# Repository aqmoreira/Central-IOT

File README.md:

# Central-IOT
Central Semafórica IOT - Projeto Hardware e Software UNIVESP

Projeto focado em explorar e praticar conceitos desenvolvidos no curso de Engenharia da Computação da UNIVESP, apresentado como projeto de TCC em Grupo.
<br>

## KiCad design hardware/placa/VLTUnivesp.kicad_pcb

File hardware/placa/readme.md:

A placa foi desenvolvida com Kicad 5.1.6

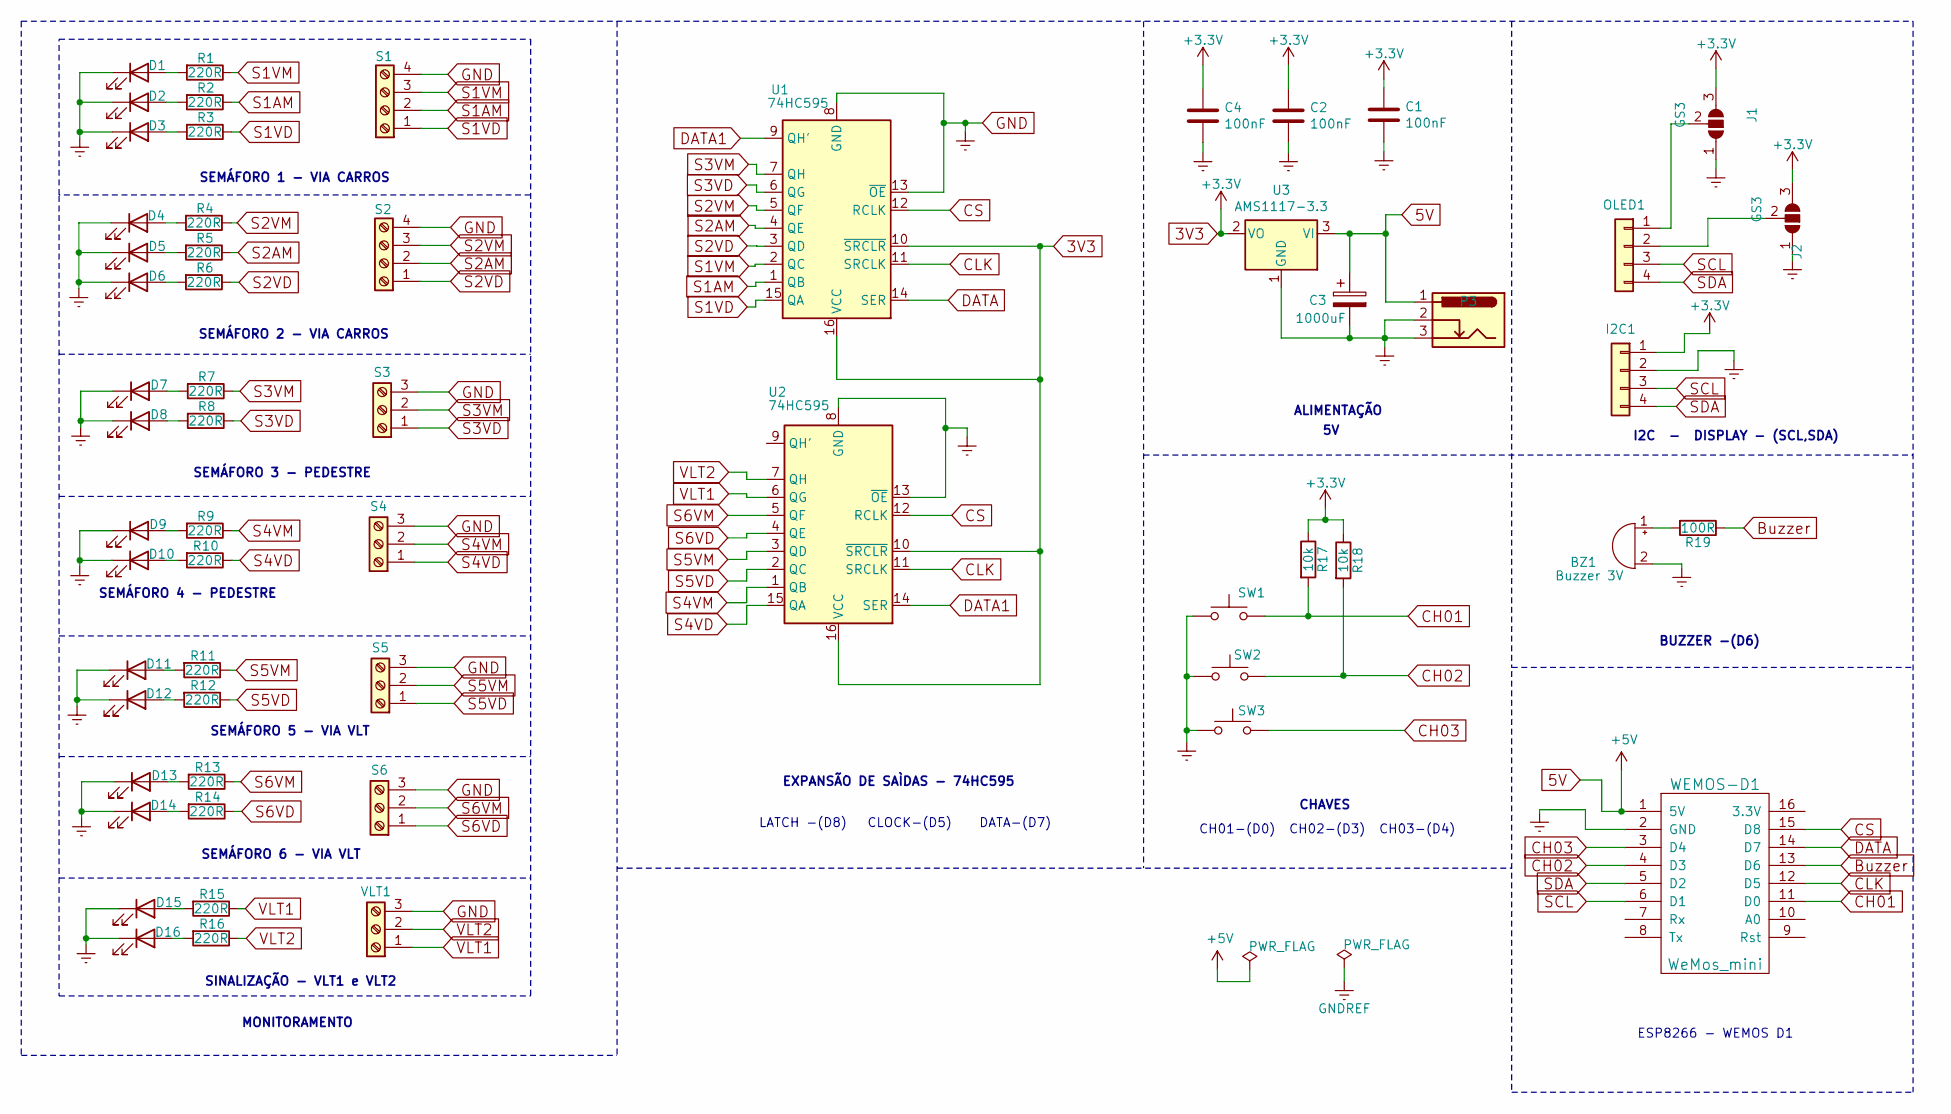
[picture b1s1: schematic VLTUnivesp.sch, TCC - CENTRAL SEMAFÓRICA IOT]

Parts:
BZ1: Buzzer 3V; Buzzer_12x9.5RM7.6
C1, C2, C4: 100nF; C_Disc_D5.0mm_W2.5mm_P5.00mm
C3: 1000uF; CP_Radial_D10.0mm_P7.50mm
D1, D4, D7, D9, D11, D13: LED; LED_D5.0mm_VM
D2, D5: LED; LED_D5.0mm_AM
D3, D6, D8, D10, D12, D14: LED; LED_D5.0mm_VD
D15: LED; LED_D5.0mm_AZ
D16: LED; LED_D5.0mm_LA
I2C1: CONN_01X04; PinSocket_1x04_P2.54mm_Vertical
J1, J2: GS3; SolderJumper-3_P1.3mm_Open_RoundedPad1.0x1.5mm_NumberLabels
OLED1: CONN_01X04; PinSocket_1x04_P2.54mm_Vertical
P3: CONN_01X03; BarrelJack_Horizontal
R1, R2, R3, R4, R5, R6, R7, R8, R9, R10, R11, R12, R13, R14, R15, R16: 220R; R_Axial_DIN0204_L3.6mm_D1.6mm_P7.62mm_Horizontal
R17, R18: 10k; R_Axial_DIN0204_L3.6mm_D1.6mm_P7.62mm_Horizontal
R19: 100R; R_Axial_DIN0204_L3.6mm_D1.6mm_P7.62mm_Horizontal
S1, S2: Screw_Terminal_01x04; KRE-1x04_P5.00mm_Horizontal
S3, S4, S5, S6: Screw_Terminal_01x03; KRE-1x03_P5.00mm_Horizontal
SW1, SW2, SW3: SW_PUSH; SW_PUSH_6mm
U1, U2: 74HC595; DIP-16_W7.62mm
U3: AMS1117-3.3; SOT-223-3_TabPin2
VLT1: Screw_Terminal_01x03; KRE-1x03_P5.00mm_Horizontal
WEMOS-D1: WeMos_mini; wemos-d1-mini-with-pin-header-and-connector

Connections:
3V3: C1.1, C2.1, C4.1, I2C1.1, J1.3 (B), J2.3 (B), R17.1, R18.1, U1.10 (~SRCLR), U1.16 (VCC), U2.10 (~SRCLR), U2.16 (VCC), U3.2 (VO)
5V: C3.1, P3.1, U3.3 (VI), WEMOS-D1.1 (5V)
Buzzer: R19.1, WEMOS-D1.13 (D6)
CH01: R17.2, SW1.2, WEMOS-D1.11 (D0)
CH02: R18.2, SW2.2, WEMOS-D1.4 (D3)
CH03: SW3.2, WEMOS-D1.3 (D4)
CLK: U1.11 (SRCLK), U2.11 (SRCLK), WEMOS-D1.12 (D5)
CS: U1.12 (RCLK), U2.12 (RCLK), WEMOS-D1.15 (D8)
DATA: U1.14 (SER), WEMOS-D1.14 (D7)
DATA1: U1.9 (QH'), U2.14 (SER)
GND: BZ1.2 (+), C1.2, C2.2, C3.2, C4.2, D1.1 (K), D2.1 (K), D3.1 (K), D4.1 (K), D5.1 (K), D6.1 (K), D7.1 (K), D8.1 (K), D9.1 (K), D10.1 (K), D11.1 (K), D12.1 (K), D13.1 (K), D14.1 (K), D15.1 (K), D16.1 (K), I2C1.2, J1.1 (A), J2.1 (A), P3.2, P3.3, S1.4, S2.4, S3.3, S4.3, S5.3, S6.3, SW1.1, SW2.1, SW3.1, U1.8 (GND), U1.13 (~OE), U2.8 (GND), U2.13 (~OE), U3.1 (GND), VLT1.3, WEMOS-D1.2 (GND)
unnamed: BZ1.1 (-), R19.2
unnamed: D1.2 (A), R1.2
unnamed: D2.2 (A), R2.2
unnamed: D3.2 (A), R3.2
unnamed: D4.2 (A), R4.2
unnamed: D5.2 (A), R5.2
unnamed: D6.2 (A), R6.2
unnamed: D7.2 (A), R7.2
unnamed: D8.2 (A), R8.2
unnamed: D9.2 (A), R9.2
unnamed: D10.2 (A), R10.2
unnamed: D11.2 (A), R11.2
unnamed: D12.2 (A), R12.2
unnamed: D13.2 (A), R13.2
unnamed: D14.2 (A), R14.2
unnamed: D15.2 (A), R15.2
unnamed: D16.2 (A), R16.2
unnamed: J1.2 (C), OLED1.1
unnamed: J2.2 (C), OLED1.2
S1AM: R2.1, S1.2, U1.1 (QB)
S1VD: R3.1, S1.1, U1.15 (QA)
S1VM: R1.1, S1.3, U1.2 (QC)
S2AM: R5.1, S2.2, U1.4 (QE)
S2VD: R6.1, S2.1, U1.3 (QD)
S2VM: R4.1, S2.3, U1.5 (QF)
S3VD: R8.1, S3.1, U1.6 (QG)
S3VM: R7.1, S3.2, U1.7 (QH)
S4VD: R10.1, S4.1, U2.15 (QA)
S4VM: R9.1, S4.2, U2.1 (QB)
S5VD: R12.1, S5.1, U2.2 (QC)
S5VM: R11.1, S5.2, U2.3 (QD)
S6VD: R14.1, S6.1, U2.4 (QE)
S6VM: R13.1, S6.2, U2.5 (QF)
SCL: I2C1.3, OLED1.3, WEMOS-D1.6 (D1)
SDA: I2C1.4, OLED1.4, WEMOS-D1.5 (D2)
VLT1: R15.1, U2.6 (QG), VLT1.1
VLT2: R16.1, U2.7 (QH), VLT1.2

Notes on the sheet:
I2C - DISPLAY - (SCL,SDA)
BUZZER -(D6)
ESP8266 - WEMOS D1
ALIMENTAÇÃO
CHAVES
SEMÁFORO 1 - VIA CARROS
SEMÁFORO 2 - VIA CARROS
SEMÁFORO 3 - PEDESTRE
SEMÁFORO 4 - PEDESTRE
SEMÁFORO 5 - VIA VLT
SEMÁFORO 6 - VIA VLT
SINALIZAÇÃO - VLT1 e VLT2
MONITORAMENTO
EXPANSÃO DE SAÌDAS - 74HC595
CH01-(D0) CH02-(D3) CH03-(D4)
LATCH -(D8) CLOCK-(D5) DATA-(D7)

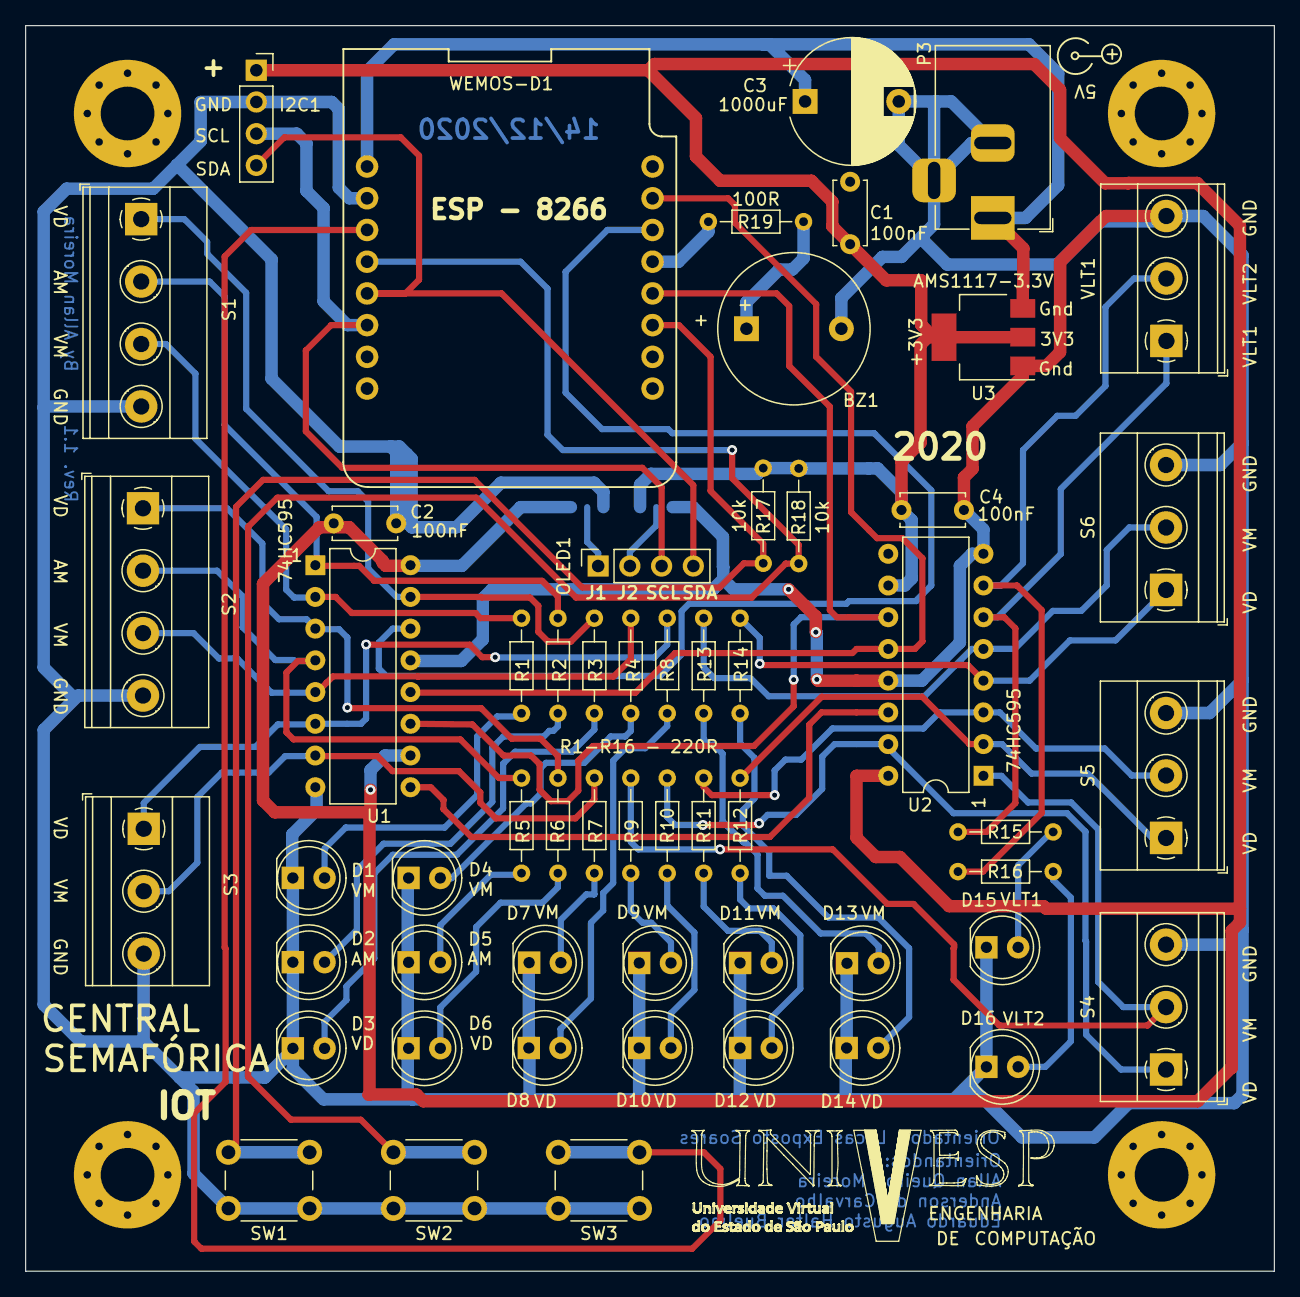
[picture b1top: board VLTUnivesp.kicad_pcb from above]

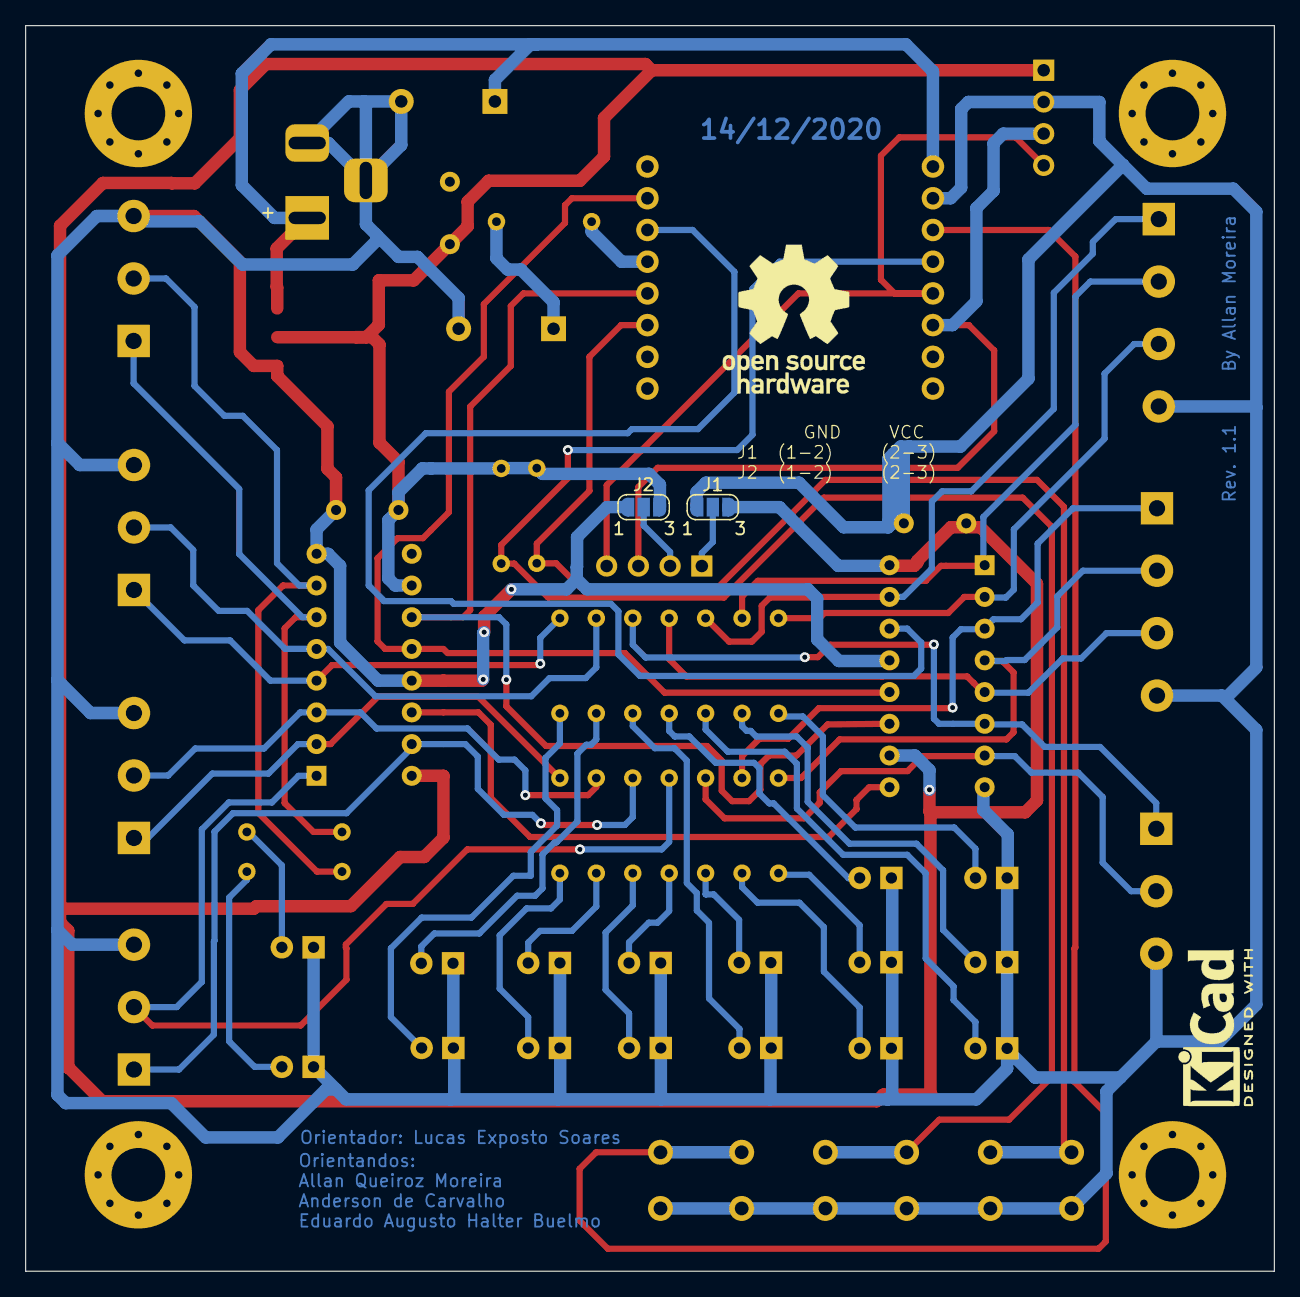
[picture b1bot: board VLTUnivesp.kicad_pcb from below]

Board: 2 copper layers, 100.0 x 99.8 mm, 59 parts (2 on the bottom side), 48 nets.

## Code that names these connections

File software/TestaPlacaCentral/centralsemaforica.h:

#define TEMPO_PISCA 500

//Chaves
#define SW1 D0
#define SW2 D3
#define SW3 D4
#define BUZZER D6

//Semaforos
//T2 T1 VM VD VM VD VM VD - Byte Superior
//VM VD VM AM VD VM AM VD - Byte Inferior

#define S1_VM 2
#define S1_AM 1
#define S1_VD 0

#define S2_VM 5
#define S2_AM 4
#define S2_VD 3

#define S3_VM 7
#define S3_VD 6

#define S4_VM 9
#define S4_VD 8

#define S5_VM 11
#define S5_VD 10

#define S6_VM 13
#define S6_VD 12

#define VLT1 14
#define VLT2 15

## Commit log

2020-10-31 Iniciando o repositório com alguns arquivos dos projeto.
2020-10-31 Atualização das fotos
2020-10-31 Versão inicial de teste das funcionalidade da placa.
2020-11-10 Versão inicial do Firmware da Central. Esta codificado para conectar Wifi, MQTT e trata reconexão ao cair. Para perfeito funcionamento é necessário adicionar a libs na pasta das bibliotecas do arduin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
2020-11-10 Melhorias: Id do cruzamento display e ao acionar SW3
2020-11-11 Inicio da máquina de Estados dos semáforos Ainda falta a parte do offline.
2020-11-11 Codificado o estados OFFline .. Agora falta tratar o eventos das zonas de rfid
2020-11-11 Acerto de um bug
2020-11-22 Essa versão inicial do simulador de VLT. Já esta integrada com MQTT.
2020-11-23 Captura dos evento ZPP,ZCV e ZPC - Falta implementar na maquina de estados.
2020-11-25 Versão com máquina de estados finalizado e operacional.
2020-11-25 Ajuste para cada simulador ter um ID , para multiplas conexões
2020-11-25 Acerto de bug na máquina de estado do semáforo e nova página simulador 4x4
2021-01-18 Set theme jekyll-theme-architect
2021-01-19 Arquivos da placa pcb e Gerber Kicad 5.0
2021-01-19 Versão em PDF dos layers da placa
2021-01-19 Ajuste documentação
2021-01-19 Imagem do simulador operando
2021-01-21 Dicas do ambiente de desenvolvimento
2021-01-21 Link para evento no servidor mqtt padrão
2021-01-21 Adicionei uma função para resetar as configurações de WIFI. Apertando a tecla SW1 + SW2 após o logo
